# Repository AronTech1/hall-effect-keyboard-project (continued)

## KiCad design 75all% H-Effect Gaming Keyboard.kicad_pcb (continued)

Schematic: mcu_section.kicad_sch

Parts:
B1: PESD5V5C1BLYL; DFN1006-2L-BI-1; MPN PESD5V5C1BLYL(ES); LCSC Part C52994083
BOOT1: SW_SPDT; SW_SPDT_PCM12; LCSC C778186
C1, C8, C18, C20: 1uF; C_0603; Voltage Rated 50V; Tolerance ±10%; Part CL10A105KB8NNNC; LCSC C15849
C2: 8.2uF; C_0603_1608Metric
C3: 4.7uF; C_0402_1005Metric; Voltage Rated 10V; Tolerance ±20%; Part CL05A475MP5NRNC; LCSC C23733
C4: 4.7uF; C_0603; Voltage Rated 16V; Tolerance ±10%; Part CL10A475KO8NNNC; LCSC C19666
C5: 47nF; C_0603; Voltage Rated 50V; Tolerance ±10%; Part CL10B473KB8NNNC; LCSC C1622
C6, C7, C10, C11, C12, C13, C14, C15, C16, C17, C19, C23, C24, C48: 10uF; C_0805; Voltage Rated 25V; Tolerance ±10%; Part CL21A106KAYNNNE; LCSC C15850
C9: 100uF; CP_EIA-7343-31_Kemet-D; LCSC C189619
C21: 120pF; C0603
C22, C33: 4.7uF; C_0805; Voltage Rated 25V; Tolerance ±10%; Part CL21A475KAQNNNE; LCSC C1779
C25: 10uF 35V; C_0603_1608Metric; LCSC C6119879
C26, C27, C28, C30, C35: 100nF; C_0603_1608Metric; LCSC C56476
C29: 1uF; C_0603_1608Metric; LCSC C1592
C34: 100nF; C_0603; Voltage Rated 50V; Tolerance ±10%; Part CC0603KRX7R9BB104; LCSC C14663
C36: 100nF; C_0402; Voltage Rated 16V; Tolerance ±10%; Part CL05B104KO5NNNC; LCSC C1525
C37, C38: 30p; C_0603_1608Metric
CN1: S2B-PH-SM4-TB; CONN-SMD_P2.00_S2B-PH-SM4-TB-LF-SN; MPN S2B-PH-SM4-TB(LF)(SN); LCSC Part C295747
D1: MMSZ5231B-7-F; SOD-123_L2.8-W1.8-LS3.7-RD; MPN MMSZ5231B-7-F; LCSC Part C85181
D2: PWR_LED; LED_0603_1608Metric; LCSC C2994781
ESD1: PRTR5V0U2X; SOT-143; LCSC C2827688
FB1: FerriteBead; L_0603_1608Metric; LCSC C780186
Indicator1: LTST-C171KSKT; LED_0805_2012Metric; MPN LTST-C171KSKT; Digi-Key_PN 160-1428-1-ND
J1: Connector, USB-TYPE-C-16P; TYPE-C-SMD_HX-TYPE-C-16PIN; LCSC C2927039
J2, J3: SWD; PinHeader_1x05_P2.54mm_Horizontal; LCSC C706868
L1: SMNR8040-1R5MT; IND-SMD_L8.0-W8.0; MPN SMNR8040-1R5MT; LCSC Part C467150
L2: XFL4015-471MEC; IND-SMD_L4.0-W4.0_XFL4020-102MEB; MPN XFL4015-471MEC; LCSC Part C18221164
NRST1: SW_Push; SW_SPST_B3U-1000P; LCSC C231329
Q1: SSM3J328R,LF; SOT-23-3_L2.9-W1.6-P1.90-LS2.8-BR; MPN SSM3J328R,LF; LCSC Part C396016
Q3: AO3401A; Q_SOT-23; Part AO3401A; LCSC C15127
Q4: 2N7002; Q_SOT-23; Part 2N7002; LCSC C8545
R1, R5: 5.1kΩ; R_0402_1005Metric; Overload Voltage (Max) 50V; Tolerance ±1%; Part 0402WGF5101TCE; LCSC C25905
R2, R3: 4.7kΩ; R_0603; Overload Voltage (Max) 75V; Tolerance ±1%; Part 0603WAF4701T5E; LCSC C23162
R4, R11, R21, R26, R29, R30, R31, R33, R34, R35, R37: 10kΩ; R_0603; Overload Voltage (Max) 75V; Tolerance ±1%; Part 0603WAF1002T5E; LCSC C25804
R6: 10k; R_0603_1608Metric; Manufacturer_Part_Number 0603WAF1002T5E; LCSC C25804
R7: 120Ω; R_0603; Overload Voltage (Max) 75V; Tolerance ±1%; Part 0603WAF1200T5E; LCSC C22787
R8: 15kΩ; R_0603; Overload Voltage (Max) 75V; Tolerance ±1%; Part 0603WAF1502T5E; LCSC C22809
R9: 1kΩ; R_0603; Overload Voltage (Max) 75V; Tolerance ±1%; Part 0603WAF1001T5E; LCSC C21190
R10, R12, R14, R15: 100kΩ; R_0603; Overload Voltage (Max) 75V; Tolerance ±1%; Part 0603WAF1003T5E; LCSC C25803
R13, R23: 1k5; R_0603_1608Metric; LCSC C22843
R16: 732kΩ; R_0603_1608Metric
R17: 163kΩ; R_0603_1608Metric
R18, R19, R20: 10k; R_0603_1608Metric; LCSC C25804
R22: 12kΩ; R_0402_1005Metric; Overload Voltage (Max) 50V; Tolerance ±1%; Part 0402WGF1202TCE; LCSC C25752
R32: 100Ω; R_0603; Overload Voltage (Max) 75V; Tolerance ±1%; Part 0603WAF1000T5E; LCSC C22775
R36: 2.2kΩ; R_0603; Overload Voltage (Max) 75V; Tolerance ±1%; Part 0603WAF2201T5E; LCSC C4190
SW2: MST-13D18G4; SW-SMD_MST-13D18G4; MPN MST-13D18G4; LCSC Part C49023771
U1: BQ25896RTWT; WQFN-24_L4.0-W4.0-P0.50-TL-EP2.7; MPN BQ25896RTWT; LCSC Part C2876371
U2: AP22653W6-7; SOT-23-6_L2.9-W1.6-P0.95-LS2.8-BR; MPN AP22653W6-7; LCSC Part C2158037
U3, U4: AP2112K-3.3TRG1; SOT-25-5_L2.9-W1.6-P0.95-LS2.8-BL; MPN AP2112K-3.3TRG1; LCSC Part C51118
U5: TPS62822DLC; Texas_VSON-HR-8_1.5x2mm_P0.5mm; LCSC Part C473385
U6: AT32F405RCT7; LQFP-64_10x10mm_P0.5mm
U8: nRF52840_holyiot_18010
U16: MAX17048G+T10; TDFN-8_L2.0-W2.0-P0.50-BL-EP1.2; MPN MAX17048G+T10; LCSC Part C2682616
Y1: X322512MSB4SI; Crystal_SMD_3225-4Pin_3.2x2.5mm

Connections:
+3.3V: BOOT1.3 (C), C21.1, C23.1, C24.1, C25.1, C26.1, C27.1, C28.1, L2.2, R2.1, R3.1, R4.1, R13.1, R16.1, R20.2, R21.1, R29.1, R30.1, R31.1, R35.1, U6.1 (VDD), U6.36 (VDD), U6.64 (VDD); also elsewhere on the board
+3.3VA: C15.1, C18.1, FB1.1, U3.5 (VOUT); also elsewhere on the board
+3V3: C16.1, C20.1, C33.1, C34.1, J3.5, U4.5 (VOUT), U8.14 (VDD_nRF)
+BATT: B1.2 (IO2), C36.1, CN1.1, Q1.3 (D), U16.2 (CELL), U16.3 (VDD)
+VSW: C6.1, C7.1, C17.1, C19.1, C22.1, L1.2, Q3.2 (S), R14.2, R15.2, R26.1, U1.15 (SYS), U1.16 (SYS), U3.1 (VIN), U4.1 (VIN), U5.1 (EN), U5.7 (VIN)
/MCU SECTION/+VBUS: C3.1, C48.1, J1.A9B4 (VBUS), J1.B9A4 (VBUS), R6.1, U2.1 (IN)
/MCU SECTION/nOCS1: U2.4 (~FAULT)
ALERT: R21.2, U6.19 (PF5), U16.5 (~ALRT)
BOOT0: R18.1, U6.60 (PF11/BOOT0)
BQ_CE: R10.1, U1.9 (~CE), U6.10 (PC2)
BQ_INT: R4.2, U1.7 (INT), U6.9 (PC1)
BQ_PSEL: R35.2, U1.2 (PSEL), U6.51 (PC10)
ENC_A: U6.17 (PA3); also elsewhere on the board
ENC_B: U6.18 (PF4); also elsewhere on the board
ENC_SW: U6.42 (PA9); also elsewhere on the board
GND: B1.1 (IO1), BOOT1.1 (A), C1.2, C2.2, C3.2, C4.2, C6.2, C7.2, C9.2, C10.2, C11.2, C12.2, C13.2, C14.2, C15.2, C16.2, C17.2, C18.2, C19.2, C20.2, C22.2, C23.2, C24.2, C25.2, C26.2, C27.2, C28.2, C29.2, C30.2, C33.2, C34.2, C35.2, C36.2, C37.2, C38.2, C48.2, CN1.2, CN1.3, CN1.4, D2.1 (K), ESD1.1 (GND), Indicator1.2, J1.A12B1 (GND), J1.B12A1 (GND), J1.S1 (SHIELD), J2.4, J3.1, NRST1.1, Q4.2 (S), R1.2, R5.2, R7.1, R8.2, R10.2, R11.2, R12.2, R17.2, R19.2, R22.2, R33.2, R37.2, SW2.3, U1.8 (OTG), U1.17 (PGND), U1.18 (PGND), U1.25 (EP), U2.2 (GND), U3.2 (GND), U4.2 (GND), U5.3 (AGND), U5.5 (PGND), U6.12 (VSSA), U6.31 (VSS), U6.63 (VSS), U8.1 (GND), U8.25 (GND), U8.37 (GND), U16.1 (CTG), U16.4 (GND), U16.6 (QSTRT), U16.9 (EP), Y1.2, Y1.4; also elsewhere on the board
HEXT_IN: C37.1, U6.5 (PF0/HEXT_IN), Y1.1
HEXT_OUT: C38.1, U6.6 (PF1/HEXT_OUT), Y1.3
IRQ: U6.26 (PB0), U8.51 (P0.17)
Indicator: R23.1, U6.62 (PB9)
LEDS_EN: R32.1, U6.32 (PB13)
MODE_24G_N: R29.2, SW2.4, U6.50 (PA15)
MODE_BT_N: R31.2, SW2.2, U6.53 (PC12)
MODE_WIRED_N: R30.2, SW2.1, U6.52 (PC11)
MUX_OUT_1: U6.11 (PC3); also elsewhere on the board
MUX_OUT_2: U6.24 (PC4); also elsewhere on the board
MUX_OUT_3: U6.25 (PC5); also elsewhere on the board
MUX_OUT_4: U6.16 (PA2); also elsewhere on the board
MUX_OUT_5: U6.14 (PA0); also elsewhere on the board
MUX_OUT_6: U6.15 (PA1); also elsewhere on the board
MUX_SELECT_0: U6.28 (PB2); also elsewhere on the board
MUX_SELECT_1: U6.29 (PB10); also elsewhere on the board
MUX_SELECT_2: U6.30 (PB12); also elsewhere on the board
MUX_SELECT_3: U6.56 (PB4); also elsewhere on the board
NRST: C35.1, J2.1, NRST1.2, U6.7 (NRST)
unnamed: BOOT1.2 (B), R18.2
unnamed: C5.1, L1.1, U1.19 (SW), U1.20 (SW)
unnamed: D1.2 (A), Q1.1 (G), R12.1
unnamed: C14.1, D1.1 (K), Q1.2 (S), U1.13 (BAT), U1.14 (BAT)
unnamed: D2.2 (A), R13.2
unnamed: Indicator1.1, R23.2
unnamed: J1.A5 (CC1), R1.1
unnamed: J1.B5 (CC2), R5.1
unnamed: C8.2, Q3.1 (G), R26.2, R36.1
unnamed: Q4.3 (D), R36.2
unnamed: Q4.1 (G), R32.2, R33.1
unnamed: C5.2, U1.21 (BTST)
unnamed: R7.2, U1.10 (ILIM)
unnamed: C2.1, U1.23 (PMID)
unnamed: R11.1, R34.2, U1.11 (TS)
unnamed: R6.2, U2.3 (EN/~EN)
unnamed: R8.1, U2.5 (ILIM)
unnamed: R14.1, U3.3 (EN)
unnamed: R15.1, U4.3 (EN)
unnamed: C21.2, R16.2, R17.1, U5.2 (FB)
unnamed: L2.1, U5.6 (SW)
unnamed: R22.1, U6.33 (OTGHS1_R)
unnamed: R9.1, U8.21 (P0.18-RESET)
PWR: U6.44 (PA11)
REIGN: C4.1, R34.1, U1.22 (REGN)
RESET: R9.2, U6.27 (PB1)
RGB_LED: U6.58 (PB6); also elsewhere on the board
RST: J3.3
SCL: R2.2, U1.5 (SCL), U6.61 (PB8), U16.7 (SCL)
SDA: R3.2, U1.6 (SDA), U6.59 (PB7), U16.8 (SDA)
SPI3_CS: U6.37 (PC6); also elsewhere on the board
SPI3_D/C: U6.38 (PC7); also elsewhere on the board
SPI3_MOSI: U6.57 (PB5); also elsewhere on the board
SPI3_SCK: U6.55 (PB3); also elsewhere on the board
SPI_CS: U6.20 (PA4), U8.54 (P0.13)
SPI_MISO: U6.22 (PA6), U8.52 (P0.15)
SPI_MOSI: U6.23 (PA7), U8.55 (P0.16)
SPI_SCK: U6.21 (PA5), U8.53 (P0.14)
SWCLK: J2.5, R19.1, U6.49 (PA14)
SWDCLK: J3.2, U8.31 (SWDCLK)
SWDIO: J2.3, R20.1, U6.46 (PA13)
SWDIO_: J3.4, U8.32 (SWDIO)
TFT_BLK: U6.41 (PA8); also elsewhere on the board
TFT_RST: U6.39 (PC8); also elsewhere on the board
USB_D+: ESD1.2 (I/O1), J1.A6 (D+), J1.B6 (D+), U6.35 (OTGHS1_D+)
USB_D-: ESD1.3 (I/O2), J1.A7 (D-), J1.B7 (D-), U6.34 (OTGHS1_D-)
VBUS: C1.1, C9.1, C10.1, C11.1, C12.1, C13.1, ESD1.4 (VCC), U1.1 (VBUS), U2.6 (OUT)
VDDA: C29.1, C30.1, FB1.2, U6.13 (VDDA)
VLED: C8.1, Q3.3 (D), R37.1; also elsewhere on the board

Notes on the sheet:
nRF52840 MCU
Battery charging IC
Caps LED
VBUS PROTECTION CIRCUIT
USB_C
Underglow enable
reverse polarity protection
Digital rail
MICROCONTROLLER
Voltage Sensing
AT32F405RCT7 MCU
Battery Connector
Analog rail
SPI
RF rail
SPI
Mode Switch

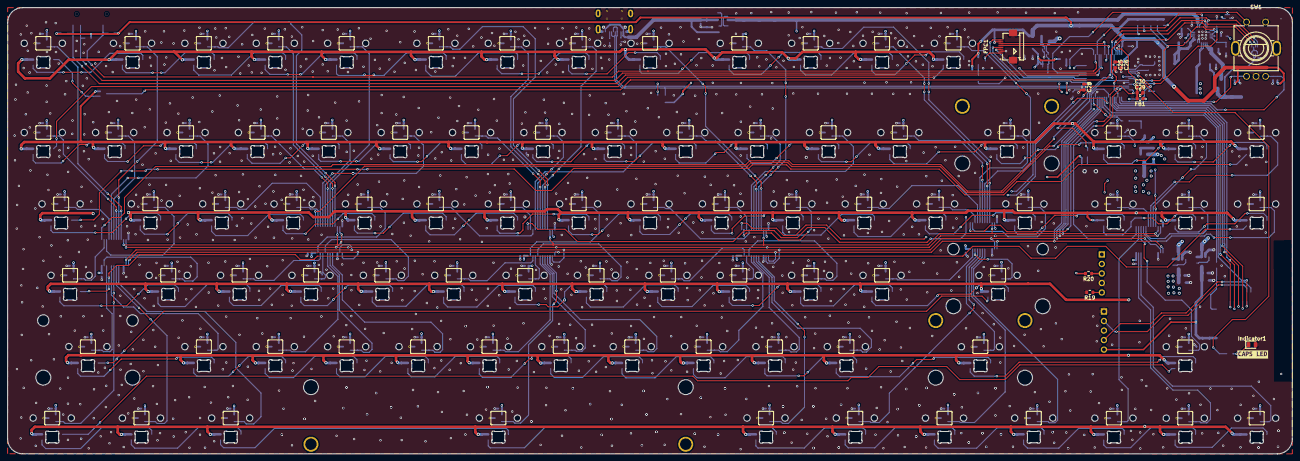
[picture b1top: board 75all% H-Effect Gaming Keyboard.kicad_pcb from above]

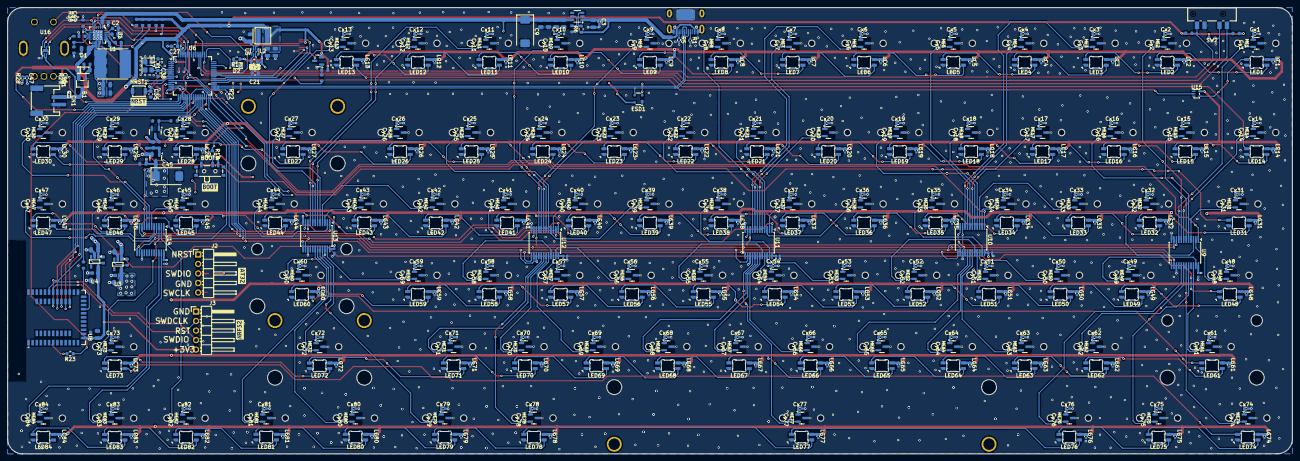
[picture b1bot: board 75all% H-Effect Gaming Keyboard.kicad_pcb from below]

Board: 4 copper layers, 342.9 x 119.1 mm, 552 parts (536 on the bottom side), 251 nets.

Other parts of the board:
kibuzzard-6AFAE696: G***; kibuzzard-6AFAE696
kibuzzard-6AFB13BB: G***; kibuzzard-6AFB13BB
kibuzzard-6AFB13D7: G***; kibuzzard-6AFB13D7
kibuzzard-6AFB142E: G***; kibuzzard-6AFB142E
kibuzzard-6AFB1407: G***; kibuzzard-6AFB1407
